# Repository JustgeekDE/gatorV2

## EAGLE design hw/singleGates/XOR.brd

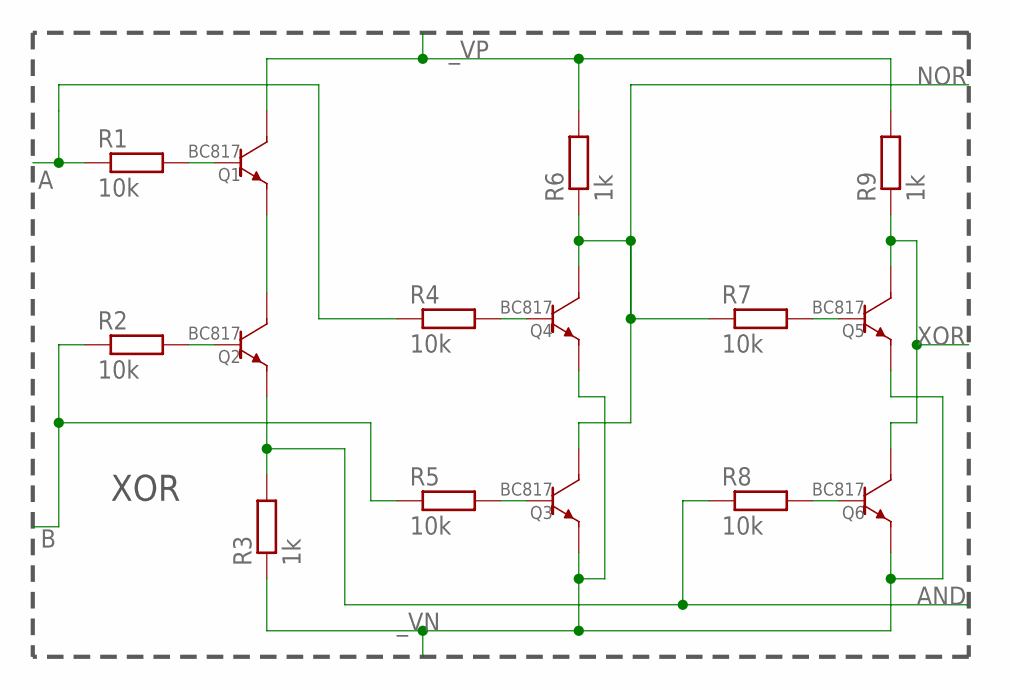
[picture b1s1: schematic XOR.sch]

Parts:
Q1, Q2, Q3, Q4, Q5, Q6: BC817; SOT23
R1, R2, R4, R5, R7, R8: 10k; R0603
R3, R6, R9: 1k; R0603

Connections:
A: R1.1, R4.1
AND: Q2.P$2 (EMITTER), R3.2, R8.1
B: R2.1, R5.1
unnamed: Q1.P$2 (EMITTER), Q2.P$3 (COLLECTOR)
unnamed: Q1.P$1 (BASE), R1.2
unnamed: Q2.P$1 (BASE), R2.2
unnamed: Q3.P$1 (BASE), R5.2
unnamed: Q4.P$1 (BASE), R4.2
unnamed: Q6.P$1 (BASE), R8.2
unnamed: Q5.P$1 (BASE), R7.2
NOR: Q3.P$3 (COLLECTOR), Q4.P$3 (COLLECTOR), R6.1, R7.1
XOR: Q5.P$3 (COLLECTOR), Q6.P$3 (COLLECTOR), R9.1
_VN: Q3.P$2 (EMITTER), Q4.P$2 (EMITTER), Q5.P$2 (EMITTER), Q6.P$2 (EMITTER), R3.1
_VP: Q1.P$3 (COLLECTOR), R6.2, R9.2

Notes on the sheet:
XOR

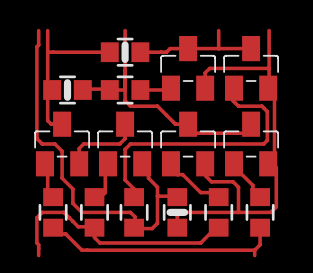
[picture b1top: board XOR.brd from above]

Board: 2 copper layers, 15 parts (0 on the bottom side), 14 nets.

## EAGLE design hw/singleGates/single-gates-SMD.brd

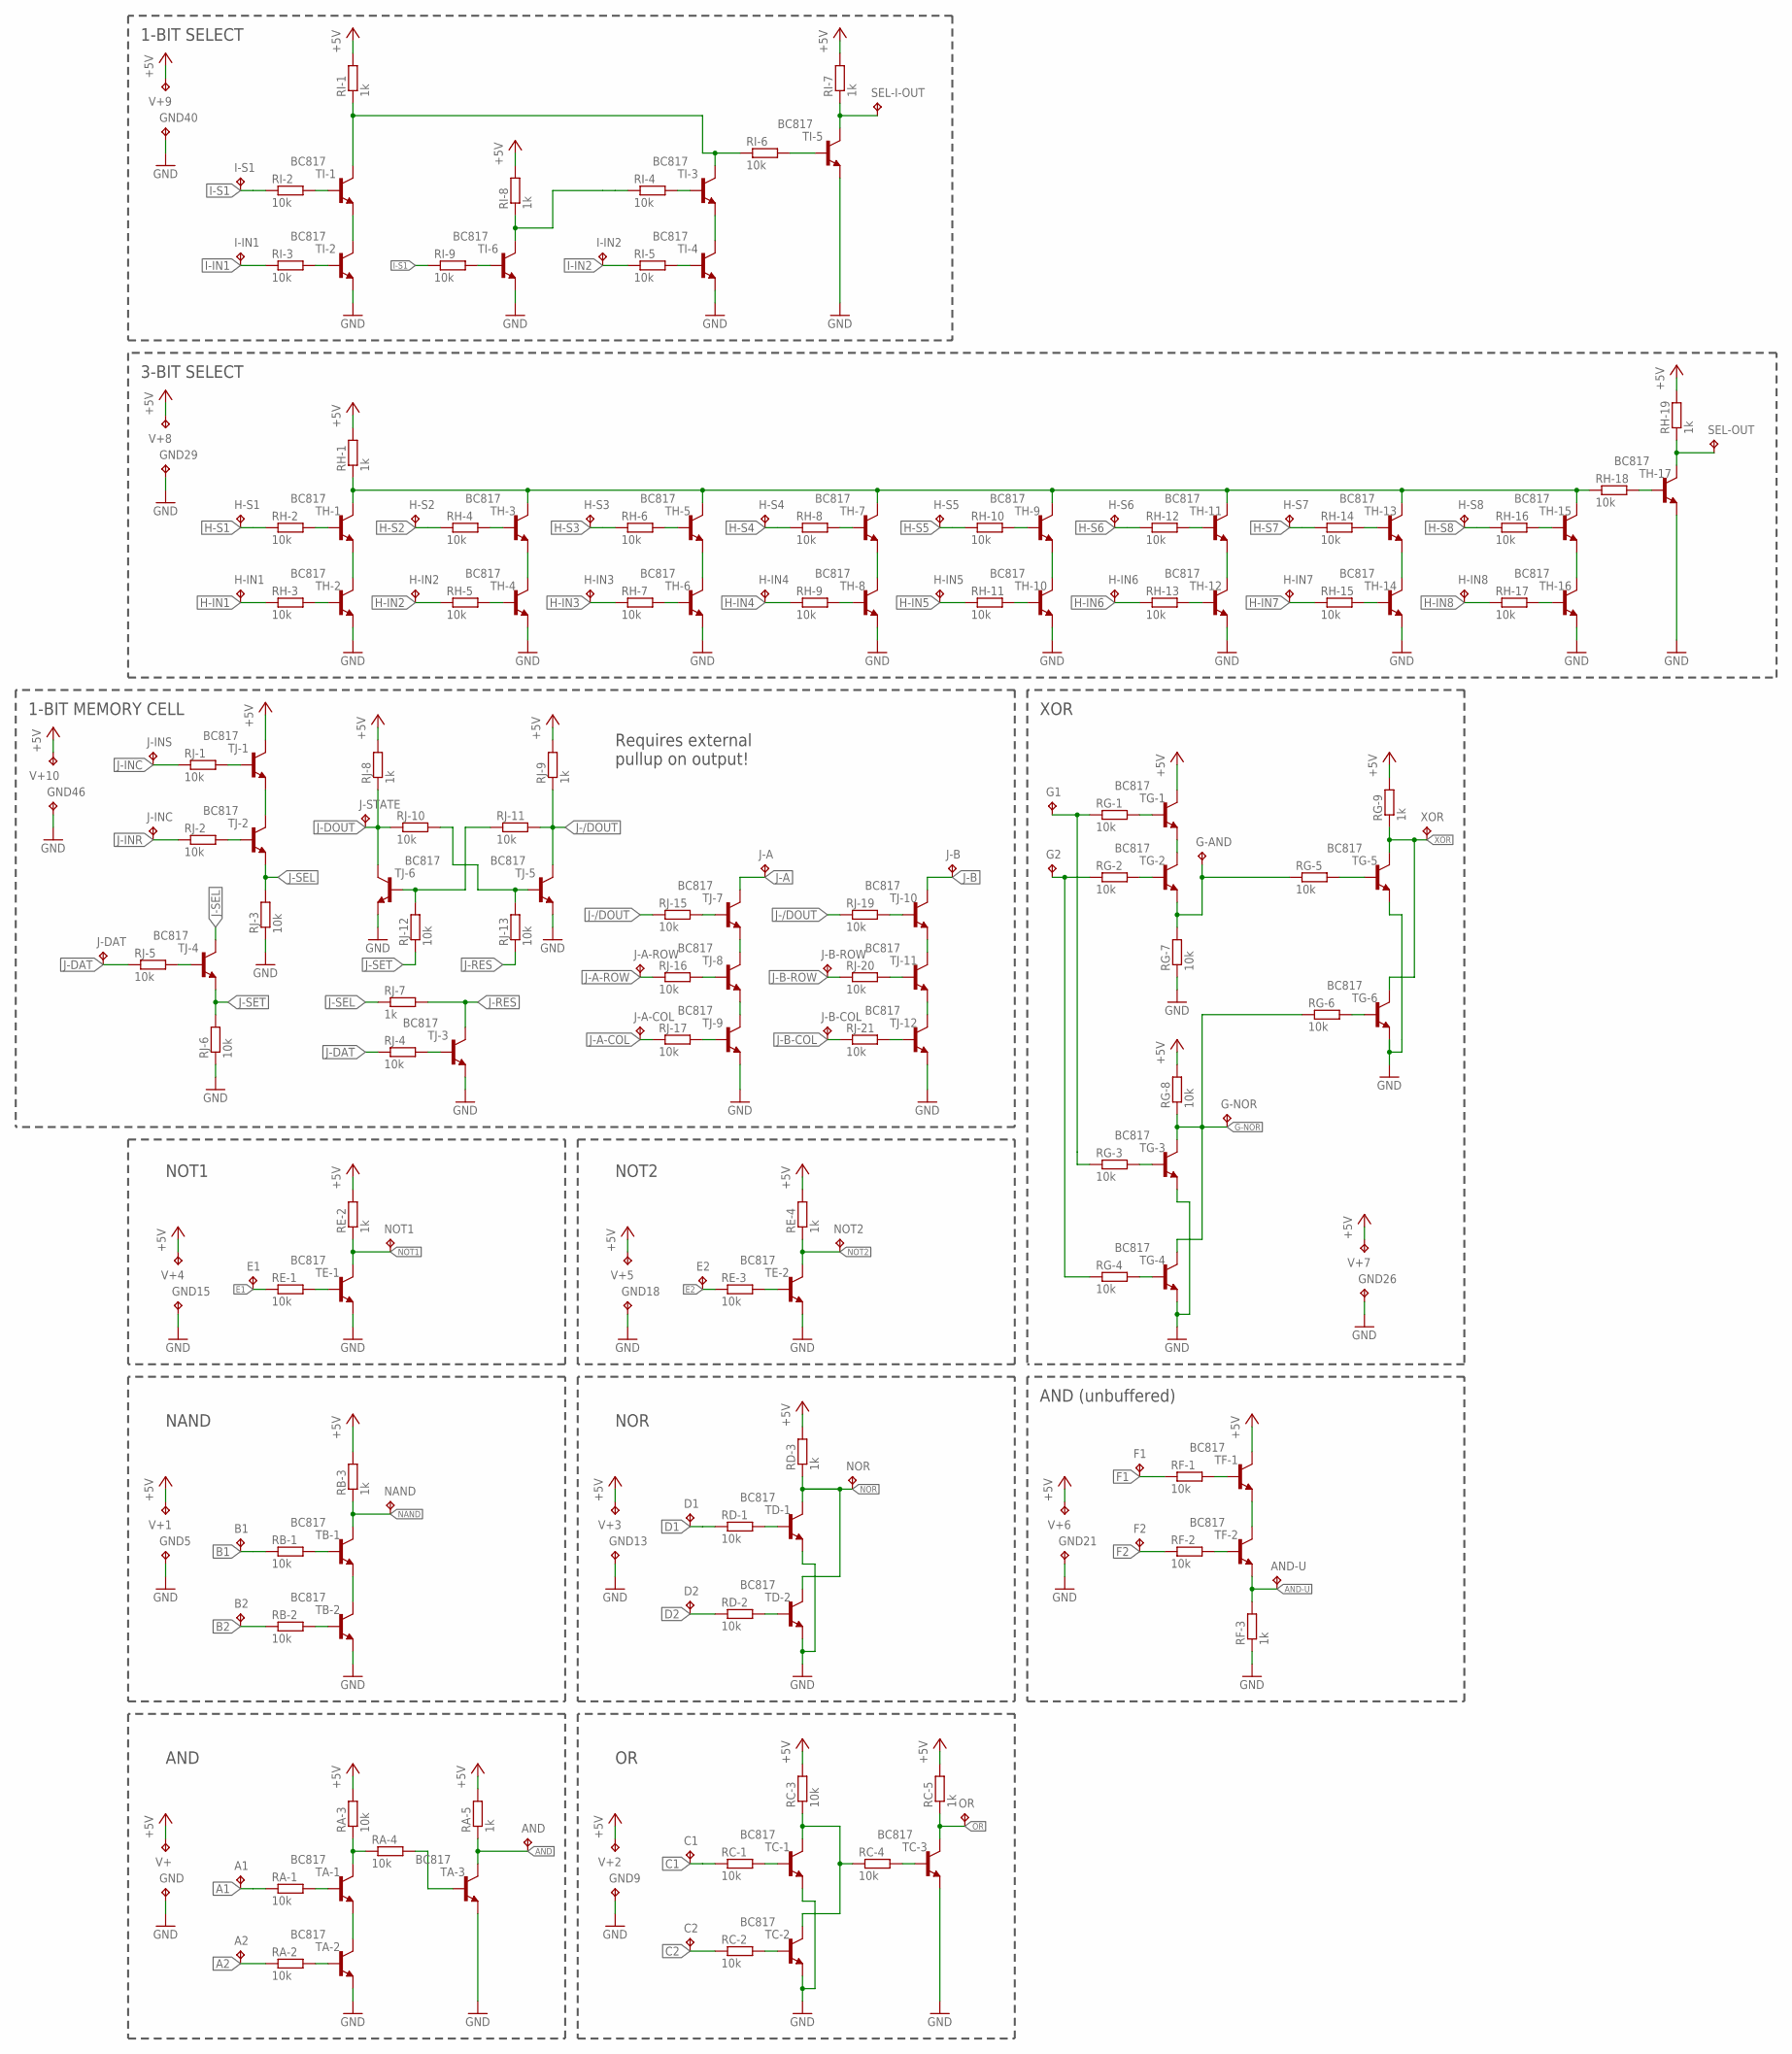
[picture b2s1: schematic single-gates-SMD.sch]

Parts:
A1, A2: TPTP07R; TP07R
AND: TPTP07R; TP07R
AND-U: TPTP07R; TP07R
B1, B2: TPTP07R; TP07R
C1, C2: TPTP07R; TP07R
D1, D2: TPTP07R; TP07R
E1, E2: TPTP07R; TP07R
F1, F2: TPTP07R; TP07R
G1, G2: TPTP07R; TP07R
G-AND: TPTP07R; TP07R
G-NOR: TPTP07R; TP07R
GND, GND5, GND9, GND13, GND15, GND18, GND21, GND26, GND29, GND40, GND46: TPTP07R; TP07R
H-IN1, H-IN2, H-IN3, H-IN4, H-IN5, H-IN6, H-IN7, H-IN8: TPTP07R; TP07R
H-S1, H-S2, H-S3, H-S4, H-S5, H-S6, H-S7, H-S8: TPTP07R; TP07R
I-IN1, I-IN2: TPTP07R; TP07R
I-S1: TPTP07R; TP07R
J-A: TPTP07R; TP07R
J-A-COL: TPTP07R; TP07R
J-A-ROW: TPTP07R; TP07R
J-B: TPTP07R; TP07R
J-B-COL: TPTP07R; TP07R
J-B-ROW: TPTP07R; TP07R
J-DAT: TPTP07R; TP07R
J-INC: TPTP07R; TP07R
J-INS: TPTP07R; TP07R
J-STATE: TPTP07R; TP07R
NAND: TPTP07R; TP07R
NOR: TPTP07R; TP07R
NOT1, NOT2: TPTP07R; TP07R
OR: TPTP07R; TP07R
RA-1, RA-2, RA-3, RA-4: 10k; R0603
RA-5: 1k; R0603
RB-1, RB-2: 10k; R0603
RB-3: 1k; R0603
RC-1, RC-2, RC-3, RC-4: 10k; R0603
RC-5: 1k; R0603
RD-1, RD-2: 10k; R0603
RD-3: 1k; R0603
RE-1, RE-3: 10k; R0603
RE-2, RE-4: 1k; R0603
RF-1, RF-2: 10k; R0603
RF-3: 1k; R0603
RG-1, RG-2, RG-3, RG-4, RG-5, RG-6, RG-7, RG-8: 10k; R0603
RG-9: 1k; R0603
RH-1, RH-19: 1k; R0603
RH-2, RH-3, RH-4, RH-5, RH-6, RH-7, RH-8, RH-9, RH-10, RH-11, RH-12, RH-13, RH-14, RH-15, RH-16, RH-17, RH-18: 10k; R0603
RI-1, RI-7, RI-8: 1k; R0603
RI-2, RI-3, RI-4, RI-5, RI-6, RI-9: 10k; R0603
RJ-1, RJ-2, RJ-3, RJ-4, RJ-5, RJ-6, RJ-10, RJ-11, RJ-12, RJ-13, RJ-15, RJ-16, RJ-17, RJ-19, RJ-20, RJ-21: 10k; R0603
RJ-7, RJ-8, RJ-9: 1k; R0603
SEL-I-OUT: TPTP07R; TP07R
SEL-OUT: TPTP07R; TP07R
TA-1, TA-2, TA-3: BC817; SOT23-BEC
TB-1, TB-2: BC817; SOT23-BEC
TC-1, TC-2, TC-3: BC817; SOT23-BEC
TD-1, TD-2: BC817; SOT23-BEC
TE-1, TE-2: BC817; SOT23-BEC
TF-1, TF-2: BC817; SOT23-BEC
TG-1, TG-2, TG-3, TG-4, TG-5, TG-6: BC817; SOT23-BEC
TH-1, TH-2, TH-3, TH-4, TH-5, TH-6, TH-7, TH-8, TH-9, TH-10, TH-11, TH-12, TH-13, TH-14, TH-15, TH-16, TH-17: BC817; SOT23-BEC
TI-1, TI-2, TI-3, TI-4, TI-5, TI-6: BC817; SOT23-BEC
TJ-1, TJ-2, TJ-3, TJ-4, TJ-5, TJ-6, TJ-7, TJ-8, TJ-9, TJ-10, TJ-11, TJ-12: BC817; SOT23-BEC
V+, V+1, V+2, V+3, V+4, V+5, V+6, V+7, V+8, V+9, V+10: TPTP07R; TP07R
XOR: TPTP07R; TP07R

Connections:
+5V: RA-3.2, RA-5.2, RB-3.2, RC-3.2, RC-5.2, RD-3.2, RE-2.2, RE-4.2, RG-8.2, RG-9.2, RH-1.2, RH-19.2, RI-1.2, RI-7.2, RI-8.2, RJ-8.2, RJ-9.2, TF-1.C, TG-1.C, TJ-1.C, V+.TP, V+1.TP, V+2.TP, V+3.TP, V+4.TP, V+5.TP, V+6.TP, V+7.TP, V+8.TP, V+9.TP, V+10.TP
A1: A1.TP, RA-1.1
A2: A2.TP, RA-2.1
AND: AND.TP, RA-5.1, TA-3.C
AND-U: AND-U.TP, RF-3.2, TF-2.E
B1: B1.TP, RB-1.1
B2: B2.TP, RB-2.1
C1: C1.TP, RC-1.1
C2: C2.TP, RC-2.1
D1: D1.TP, RD-1.1
D2: D2.TP, RD-2.1
E1: E1.TP, RE-1.1
E2: E2.TP, RE-3.1
F1: F1.TP, RF-1.1
F2: F2.TP, RF-2.1
G-AND: G-AND.TP, RG-5.1, RG-7.2, TG-2.E
G-NOR: G-NOR.TP, RG-6.1, RG-8.1, TG-3.C, TG-4.C
GND: GND.TP, GND5.TP, GND9.TP, GND13.TP, GND15.TP, GND18.TP, GND21.TP, GND26.TP, GND29.TP, GND40.TP, GND46.TP, RF-3.1, RG-7.1, RJ-3.1, RJ-6.1, TA-2.E, TA-3.E, TB-2.E, TC-1.E, TC-2.E, TC-3.E, TD-1.E, TD-2.E, TE-1.E, TE-2.E, TG-3.E, TG-4.E, TG-5.E, TG-6.E, TH-2.E, TH-4.E, TH-6.E, TH-8.E, TH-10.E, TH-12.E, TH-14.E, TH-16.E, TH-17.E, TI-2.E, TI-4.E, TI-5.E, TI-6.E, TJ-3.E, TJ-5.E, TJ-6.E, TJ-9.E, TJ-12.E
H-IN1: H-IN1.TP, RH-3.1
H-IN2: H-IN2.TP, RH-5.1
H-IN3: H-IN3.TP, RH-7.1
H-IN4: H-IN4.TP, RH-9.1
H-IN5: H-IN5.TP, RH-11.1
H-IN6: H-IN6.TP, RH-13.1
H-IN7: H-IN7.TP, RH-15.1
H-IN8: H-IN8.TP, RH-17.1
H-S1: H-S1.TP, RH-2.1
H-S2: H-S2.TP, RH-4.1
H-S3: H-S3.TP, RH-6.1
H-S4: H-S4.TP, RH-8.1
H-S5: H-S5.TP, RH-10.1
H-S6: H-S6.TP, RH-12.1
H-S7: H-S7.TP, RH-14.1
H-S8: H-S8.TP, RH-16.1
I-IN1: I-IN1.TP, RI-3.1
I-IN2: I-IN2.TP, RI-5.1
I-S1: I-S1.TP, RI-2.1, RI-9.1
I-S2: RI-4.1, RI-8.1, TI-6.C
J-/DOUT: RJ-9.1, RJ-11.2, RJ-15.1, RJ-19.1, TJ-5.C
J-A: J-A.TP, TJ-7.C
J-A-COL: J-A-COL.TP, RJ-17.1
J-A-ROW: J-A-ROW.TP, RJ-16.1
J-B: J-B.TP, TJ-10.C
J-B-COL: J-B-COL.TP, RJ-21.1
J-B-ROW: J-B-ROW.TP, RJ-20.1
J-DAT: J-DAT.TP, RJ-4.1, RJ-5.1
J-DOUT: J-STATE.TP, RJ-8.1, RJ-10.1, TJ-6.C
J-INC: J-INS.TP, RJ-1.1
J-INR: J-INC.TP, RJ-2.1
J-RES: RJ-7.2, RJ-13.1, TJ-3.C
J-SEL: RJ-3.2, RJ-7.1, TJ-2.E, TJ-4.C
J-SET: RJ-6.2, RJ-12.1, TJ-4.E
unnamed: RA-1.2, TA-1.B
unnamed: RA-3.1, RA-4.1, TA-1.C
unnamed: RA-2.2, TA-2.B
unnamed: TA-1.E, TA-2.C
unnamed: RB-1.2, TB-1.B
unnamed: RB-2.2, TB-2.B
unnamed: RC-1.2, TC-1.B
unnamed: TB-1.E, TB-2.C
unnamed: RC-2.2, TC-2.B
unnamed: RC-4.2, TC-3.B
unnamed: RC-3.1, RC-4.1, TC-1.C, TC-2.C
unnamed: RD-1.2, TD-1.B
unnamed: RD-2.2, TD-2.B
unnamed: RE-1.2, TE-1.B
unnamed: RA-4.2, TA-3.B
unnamed: RE-3.2, TE-2.B
unnamed: RF-1.2, TF-1.B
unnamed: RF-2.2, TF-2.B
unnamed: TG-1.E, TG-2.C
unnamed: TF-1.E, TF-2.C
unnamed: RG-1.2, TG-1.B
unnamed: RG-2.2, TG-2.B
unnamed: RG-4.2, TG-4.B
unnamed: RG-3.2, TG-3.B
unnamed: RG-6.2, TG-6.B
unnamed: RG-5.2, TG-5.B
unnamed: RH-2.2, TH-1.B
unnamed: RH-3.2, TH-2.B
unnamed: TH-1.E, TH-2.C
unnamed: G1.TP, RG-1.1, RG-3.1
unnamed: G2.TP, RG-2.1, RG-4.1
unnamed: RH-4.2, TH-3.B
unnamed: RH-5.2, TH-4.B
unnamed: TH-3.E, TH-4.C
unnamed: RH-6.2, TH-5.B
unnamed: RH-7.2, TH-6.B
unnamed: TH-5.E, TH-6.C
unnamed: RH-8.2, TH-7.B
unnamed: RH-9.2, TH-8.B
unnamed: TH-7.E, TH-8.C
unnamed: RH-10.2, TH-9.B
unnamed: RH-11.2, TH-10.B
unnamed: TH-9.E, TH-10.C
unnamed: RH-12.2, TH-11.B
unnamed: RH-13.2, TH-12.B
unnamed: TH-11.E, TH-12.C
unnamed: RH-14.2, TH-13.B
unnamed: RH-15.2, TH-14.B
unnamed: TH-13.E, TH-14.C
unnamed: RH-16.2, TH-15.B
unnamed: RH-17.2, TH-16.B
unnamed: TH-15.E, TH-16.C
unnamed: RI-2.2, TI-1.B
unnamed: RH-18.2, TH-17.B
unnamed: RI-3.2, TI-2.B
unnamed: TI-1.E, TI-2.C
unnamed: RI-4.2, TI-3.B
unnamed: RI-5.2, TI-4.B
unnamed: TI-3.E, TI-4.C
unnamed: RI-6.2, TI-5.B
unnamed: RJ-1.2, TJ-1.B
unnamed: RI-9.2, TI-6.B
unnamed: RJ-2.2, TJ-2.B
unnamed: TJ-1.E, TJ-2.C
unnamed: RJ-4.2, TJ-3.B
unnamed: RJ-5.2, TJ-4.B
unnamed: TJ-10.E, TJ-11.C
unnamed: TJ-7.E, TJ-8.C
unnamed: RJ-11.1, RJ-12.2, TJ-6.B
unnamed: RJ-10.2, RJ-13.2, TJ-5.B
unnamed: TJ-8.E, TJ-9.C
unnamed: RJ-15.2, TJ-7.B
unnamed: RJ-16.2, TJ-8.B
unnamed: RJ-17.2, TJ-9.B
unnamed: TJ-11.E, TJ-12.C
unnamed: RJ-19.2, TJ-10.B
unnamed: RJ-20.2, TJ-11.B
unnamed: RJ-21.2, TJ-12.B
NAND: NAND.TP, RB-3.1, TB-1.C
NOR: NOR.TP, RD-3.1, TD-1.C, TD-2.C
NOT1: NOT1.TP, RE-2.1, TE-1.C
NOT2: NOT2.TP, RE-4.1, TE-2.C
OR: OR.TP, RC-5.1, TC-3.C
SEL_INT: RH-1.1, RH-18.1, TH-1.C, TH-3.C, TH-5.C, TH-7.C, TH-9.C, TH-11.C, TH-13.C, TH-15.C
SEL_INT1: RI-1.1, RI-6.1, TI-1.C, TI-3.C
SEL_OUT: RH-19.1, SEL-OUT.TP, TH-17.C
SEL_OUT1: RI-7.1, SEL-I-OUT.TP, TI-5.C
XOR: RG-9.1, TG-5.C, TG-6.C, XOR.TP

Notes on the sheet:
AND
NAND
NOR
NOT1
NOT2
AND (unbuffered)
XOR
3-BIT SELECT
1-BIT SELECT
1-BIT MEMORY CELL
Requires external pullup on output!

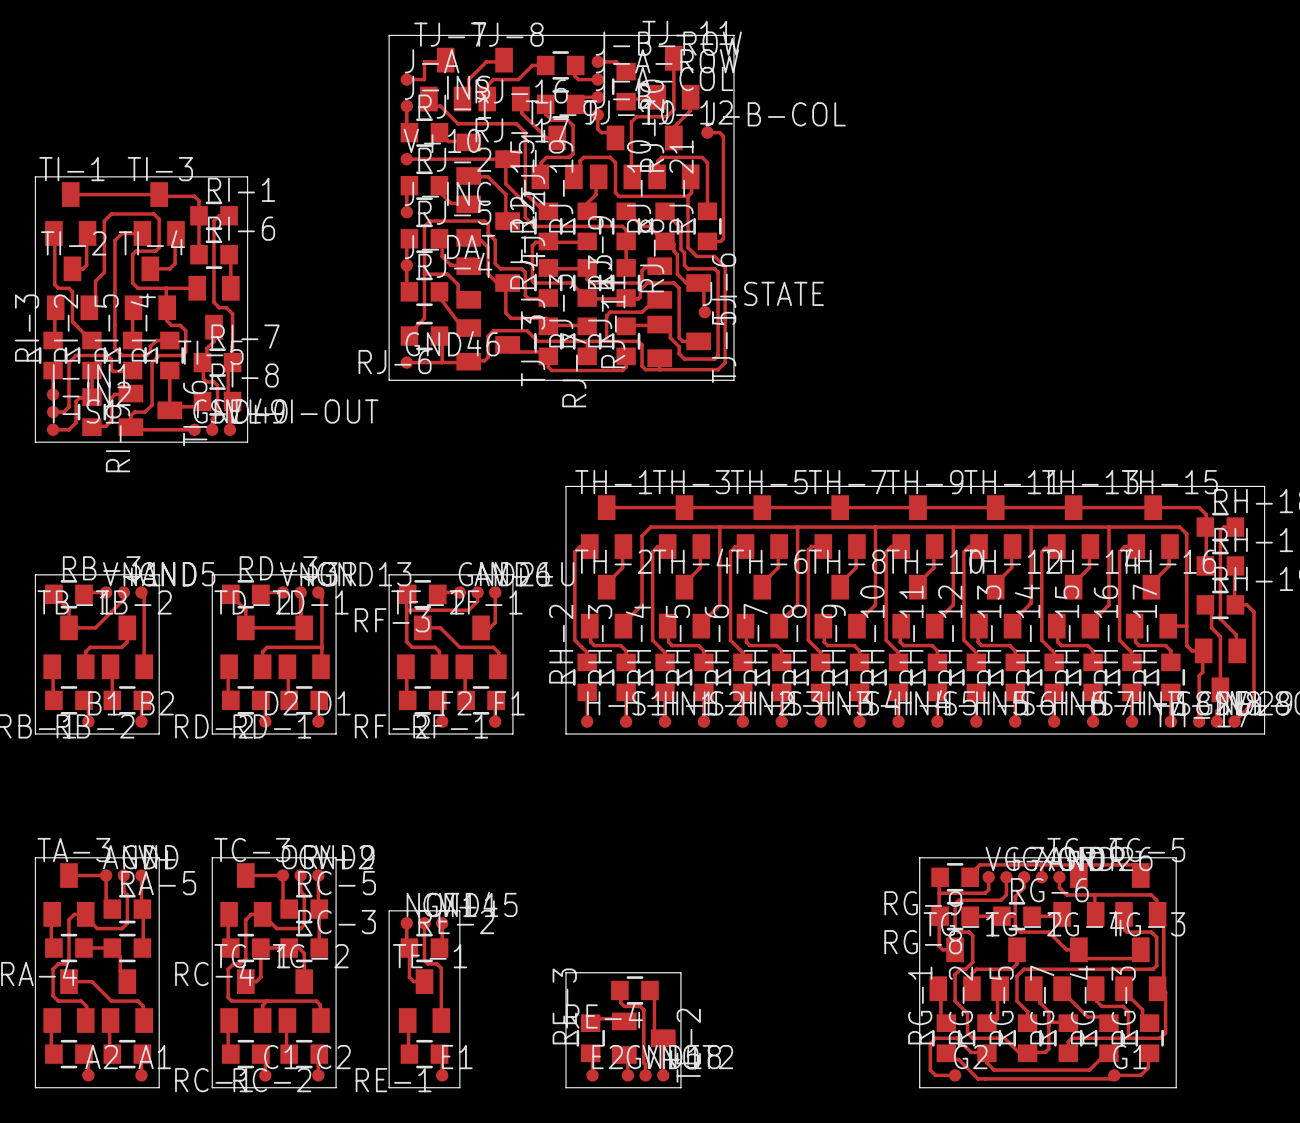
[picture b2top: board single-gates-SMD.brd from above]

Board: 2 copper layers, 69.5 x 59.5 mm, 211 parts (0 on the bottom side), 140 nets.
